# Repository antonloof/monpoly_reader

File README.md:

# monpoly_reader
Projekt ligger i det runda arkivet. RFID var krångligare än väntat
"the juice is not worth the squeze"

Spela monopol fast långsamare

och utan ett o

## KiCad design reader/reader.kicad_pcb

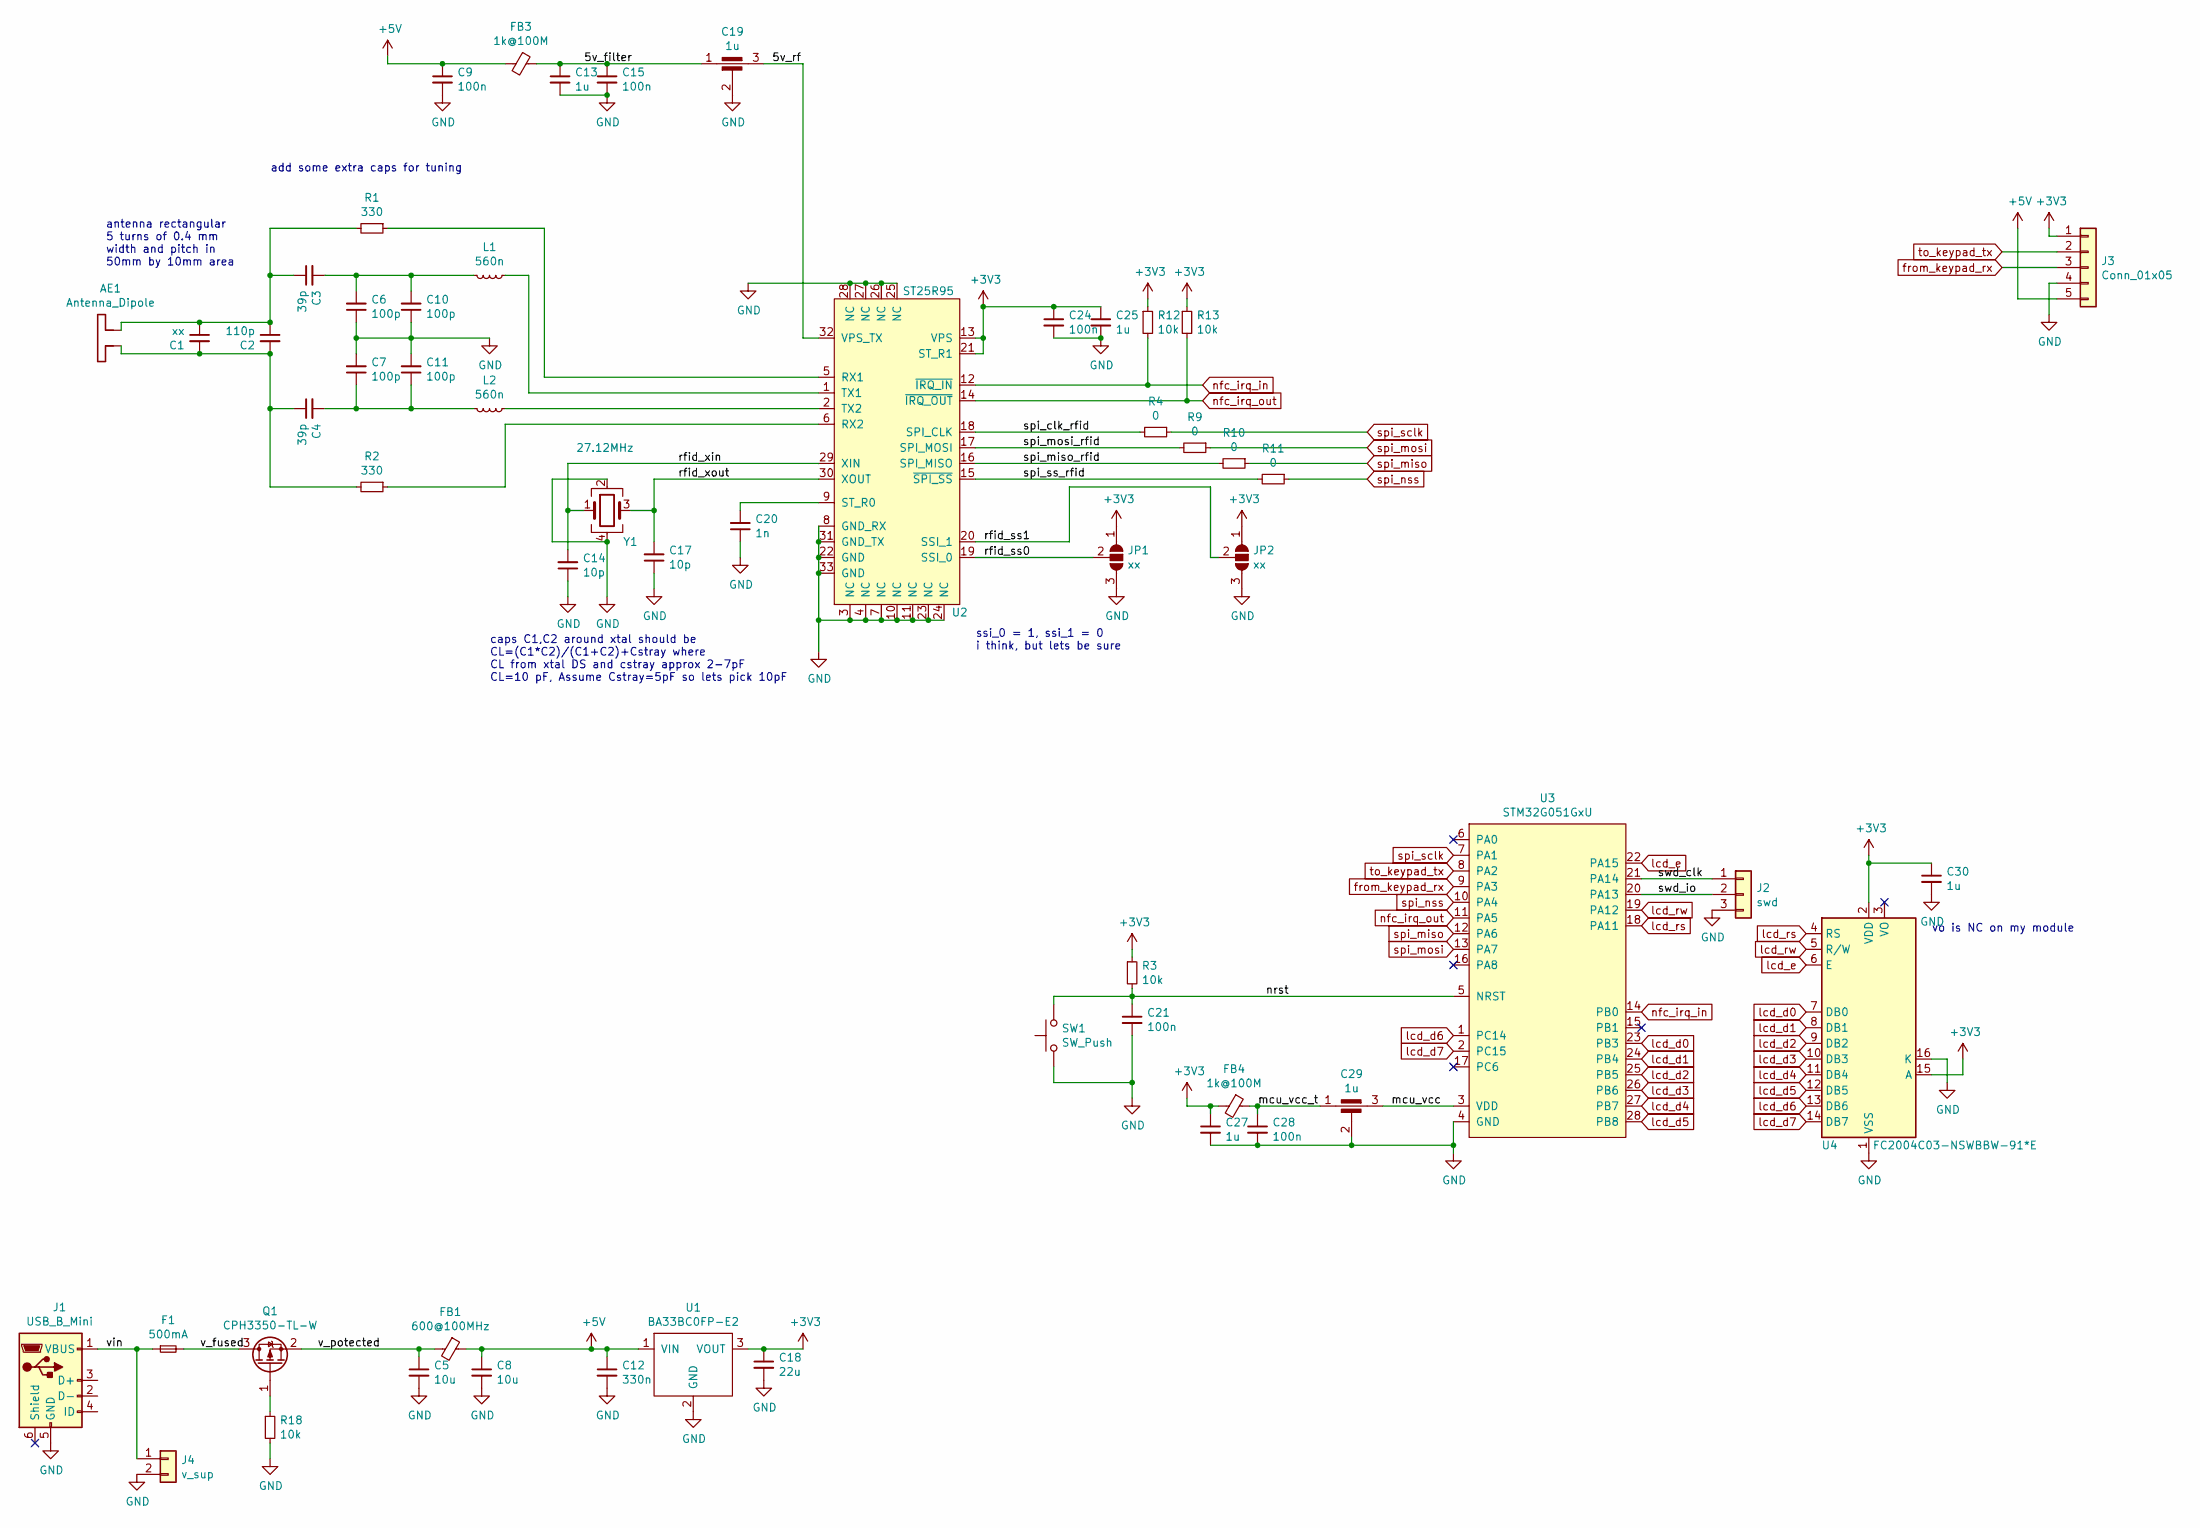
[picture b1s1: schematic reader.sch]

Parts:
AE1: Antenna_Dipole; antenna_1m_07mm_3turn
C1: xx; C_0603_1608Metric_Pad1.05x0.95mm_HandSolder
C2: 110p; C_0603_1608Metric_Pad1.05x0.95mm_HandSolder
C3, C4: 39p; C_0603_1608Metric_Pad1.05x0.95mm_HandSolder
C5, C8: 10u; C_0603_1608Metric_Pad1.05x0.95mm_HandSolder; farnell 3013453
C6, C7, C10, C11: 100p; C_0603_1608Metric_Pad1.05x0.95mm_HandSolder
C9, C15, C21, C24, C28: 100n; C_0603_1608Metric_Pad1.05x0.95mm_HandSolder
C12: 330n; C_0603_1608Metric_Pad1.05x0.95mm_HandSolder
C13, C27, C30: 1u; C_0603_1608Metric_Pad1.05x0.95mm_HandSolder; farnell 3013382
C14, C17: 10p; C_0603_1608Metric_Pad1.05x0.95mm_HandSolder
C18: 22u; C_0603_1608Metric_Pad1.05x0.95mm_HandSolder
C19, C29: 1u; NFM18PS105R0J3D
C20: 1n; C_0603_1608Metric_Pad1.05x0.95mm_HandSolder
C25: 1u; C_0603_1608Metric_Pad1.05x0.95mm_HandSolder
F1: 500mA; Fuse_1210_3225Metric
FB1: 600@100MHz; L_0603_1608Metric_Pad1.05x0.95mm_HandSolder
FB3, FB4: 1k@100M; L_0603_1608Metric_Pad1.05x0.95mm_HandSolder
J1: USB_B_Mini; USB_MICRO_10118193-0001LF
J2: swd; PinHeader_1x03_P2.54mm_Vertical
J3: Conn_01x05; PinHeader_1x05_P2.54mm_Vertical
J4: v_sup; JST_NV_B02P-NV_1x02_P5.00mm_Vertical
JP1, JP2: xx; SolderJumper-3_P1.3mm_Open_RoundedPad1.0x1.5mm
L1, L2: 560n; L_0805_2012Metric; farnell 2858966
Q1: CPH3350-TL-W; SOT-23_Handsoldering
R1, R2: 330; R_0603_1608Metric_Pad1.05x0.95mm_HandSolder
R3, R12, R13, R18: 10k; R_0603_1608Metric_Pad1.05x0.95mm_HandSolder
R4, R9, R10, R11: 0; R_0603_1608Metric_Pad1.05x0.95mm_HandSolder
SW1: SW_Push; push_sw_purple
U1: BA33BC0FP-E2; TO-252-3_TabPin2
U2: ST25R95; QFN-32-1EP_5x5mm_P0.5mm_EP3.65x3.65mm
U3: STM32G051GxU; QFN-28_4x4mm_P0.5mm
U4: FC2004C03-NSWBBW-91*E; FC2004C03-NSWBBW-91
Y1: 27.12MHz; Crystal_SMD_2016-4Pin_2.0x1.6mm

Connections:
+3V3: C18.1, C24.1, C25.1, C27.1, C30.1, FB4.2, J3.1, JP1.1 (A), JP2.1 (A), R3.1, R12.1, R13.1, U1.3 (VOUT), U2.13 (VPS), U2.21 (ST_R1), U4.2 (VDD), U4.15 (A)
+5V: C8.1, C9.1, C12.1, FB1.1, FB3.2, J3.5, U1.1 (VIN)
/5v_filter: C13.1, C15.1, C19.1, FB3.1
/5v_rf: C19.3, U2.32 (VPS_TX)
/mcu_vcc: C29.3, U3.3 (VDD)
/mcu_vcc_t: C28.1, C29.1, FB4.1
/nrst: C21.1, R3.2, SW1.2, U3.5 (NRST)
/rfid_ss0: JP1.2 (C), U2.19 (SSI_0)
/rfid_ss1: JP2.2 (C), U2.20 (SSI_1)
/rfid_xin: C14.2, U2.29 (XIN), Y1.1
/rfid_xout: C17.2, U2.30 (XOUT), Y1.3
/spi_clk_rfid: R4.2, U2.18 (SPI_CLK)
/spi_miso_rfid: R10.2, U2.16 (SPI_MISO)
/spi_mosi_rfid: R9.2, U2.17 (SPI_MOSI)
/spi_ss_rfid: R11.2, U2.15 (~SPI_SS)
/swd_clk: J2.1, U3.21 (PA14)
/swd_io: J2.2, U3.20 (PA13)
/v_fused: F1.2, Q1.3 (D)
/v_potected: C5.1, FB1.2, Q1.2 (S)
/vin: F1.1, J1.1 (VBUS), J4.1
GND: C5.2, C6.1, C7.2, C8.2, C9.2, C10.1, C11.2, C12.2, C13.2, C14.1, C15.2, C17.1, C18.2, C19.2, C20.1, C21.2, C24.2, C25.2, C27.2, C28.2, C29.2, C30.2, J1.5 (GND), J2.3, J3.4, J4.2, JP1.3 (B), JP2.3 (B), R18.2, SW1.1, U1.2 (GND), U2.3 (NC), U2.4 (NC), U2.7 (NC), U2.8 (GND_RX), U2.10 (NC), U2.11 (NC), U2.22 (GND), U2.23 (NC), U2.24 (NC), U2.25 (NC), U2.26 (NC), U2.27 (NC), U2.28 (NC), U2.31 (GND_TX), U2.33 (GND), U3.4 (GND), U4.1 (VSS), U4.16 (K), Y1.2, Y1.4
unnamed: AE1.1, C1.2, C2.2, C4.1, R2.2
unnamed: AE1.2, C1.1, C2.1, C3.1, R1.2
unnamed: C3.2, C6.2, C10.2, L1.2
unnamed: C4.2, C7.1, C11.1, L2.2
unnamed: C20.2, U2.9 (ST_R0)
unnamed: L1.1, U2.1 (TX1)
unnamed: L2.1, U2.2 (TX2)
unnamed: Q1.1 (G), R18.1
unnamed: R1.1, U2.5 (RX1)
unnamed: R2.1, U2.6 (RX2)
from_keypad_rx: J3.3, U3.9 (PA3)
lcd_d0: U3.23 (PB3), U4.7 (DB0)
lcd_d1: U3.24 (PB4), U4.8 (DB1)
lcd_d2: U3.25 (PB5), U4.9 (DB2)
lcd_d3: U3.26 (PB6), U4.10 (DB3)
lcd_d4: U3.27 (PB7), U4.11 (DB4)
lcd_d5: U3.28 (PB8), U4.12 (DB5)
lcd_d6: U3.1 (PC14), U4.13 (DB6)
lcd_d7: U3.2 (PC15), U4.14 (DB7)
lcd_e: U3.22 (PA15), U4.6 (E)
lcd_rs: U3.18 (PA11), U4.4 (RS)
lcd_rw: U3.19 (PA12), U4.5 (R/W)
nfc_irq_in: R12.2, U2.12 (~IRQ_IN), U3.14 (PB0)
nfc_irq_out: R13.2, U2.14 (~IRQ_OUT), U3.11 (PA5)
spi_miso: R10.1, U3.12 (PA6)
spi_mosi: R9.1, U3.13 (PA7)
spi_nss: R11.1, U3.10 (PA4)
spi_sclk: R4.1, U3.7 (PA1)
to_keypad_tx: J3.2, U3.8 (PA2)

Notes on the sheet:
add some extra caps for tuning
antenna rectangular 5 turns of 0.4 mm width and pitch in 50mm by 10mm area
ssi_0 = 1, ssi_1 = 0 i think, but lets be sure
caps C1,C2 around xtal should be CL=(C1*C2)/(C1+C2)+Cstray where CL from xtal DS and cstray approx 2-7pF CL=10 pF, Assume Cstray=5pF so lets pick 10pF
vo is NC on my module

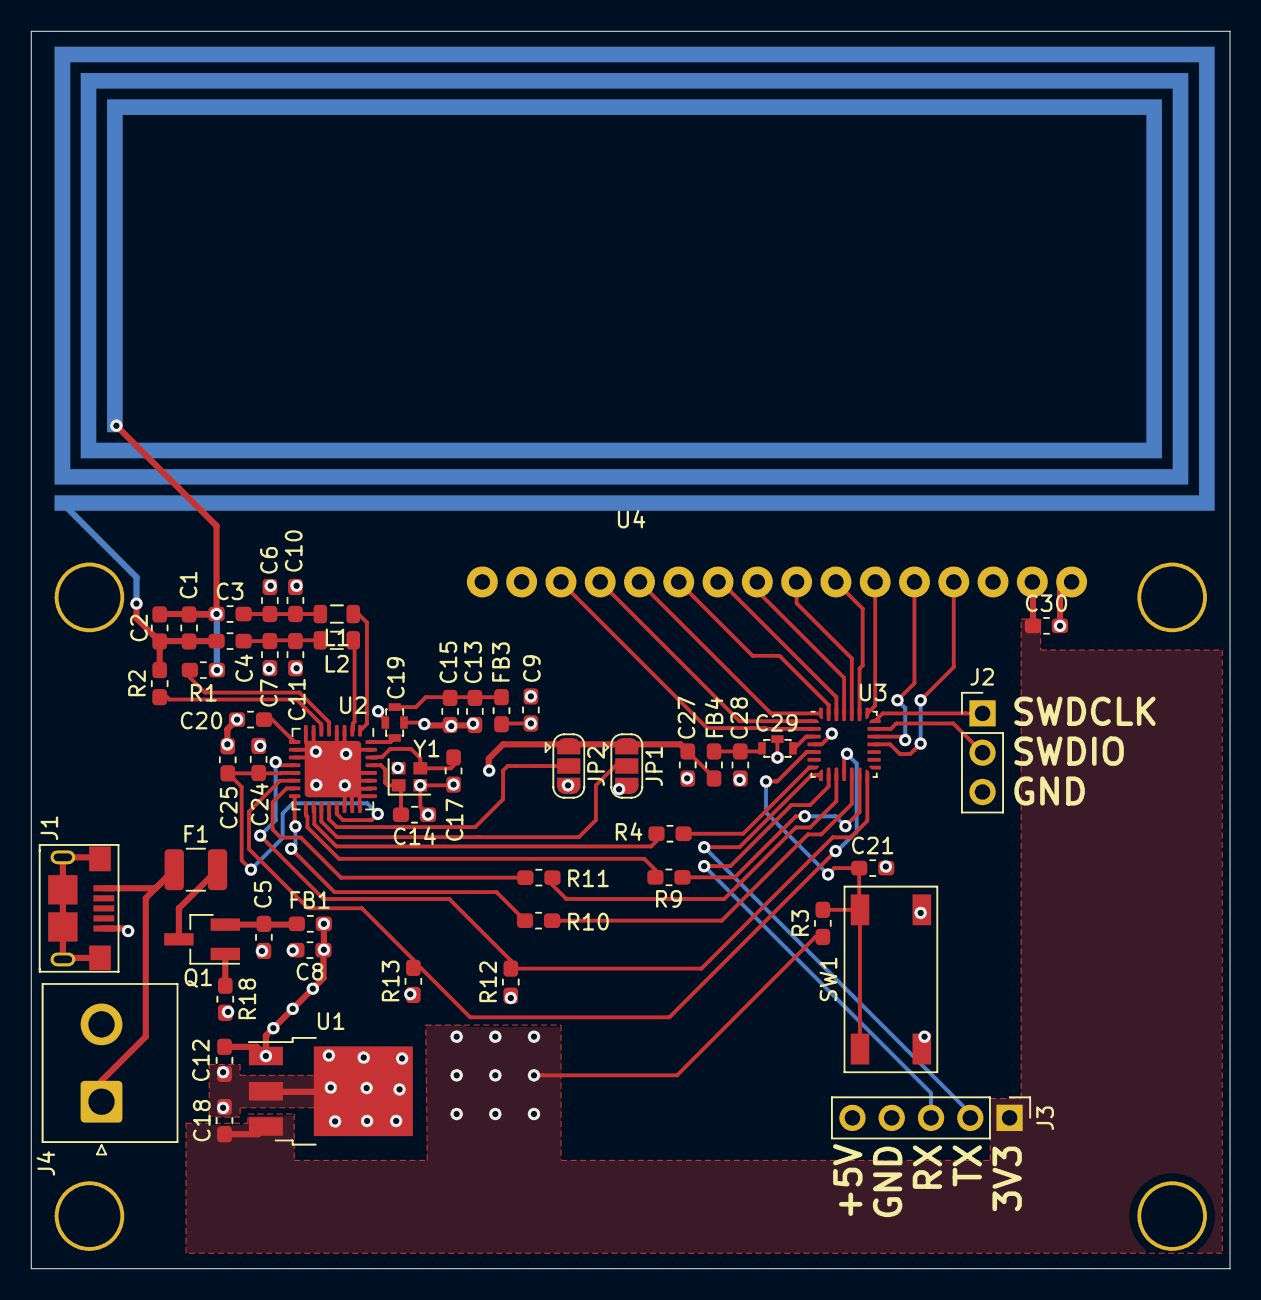
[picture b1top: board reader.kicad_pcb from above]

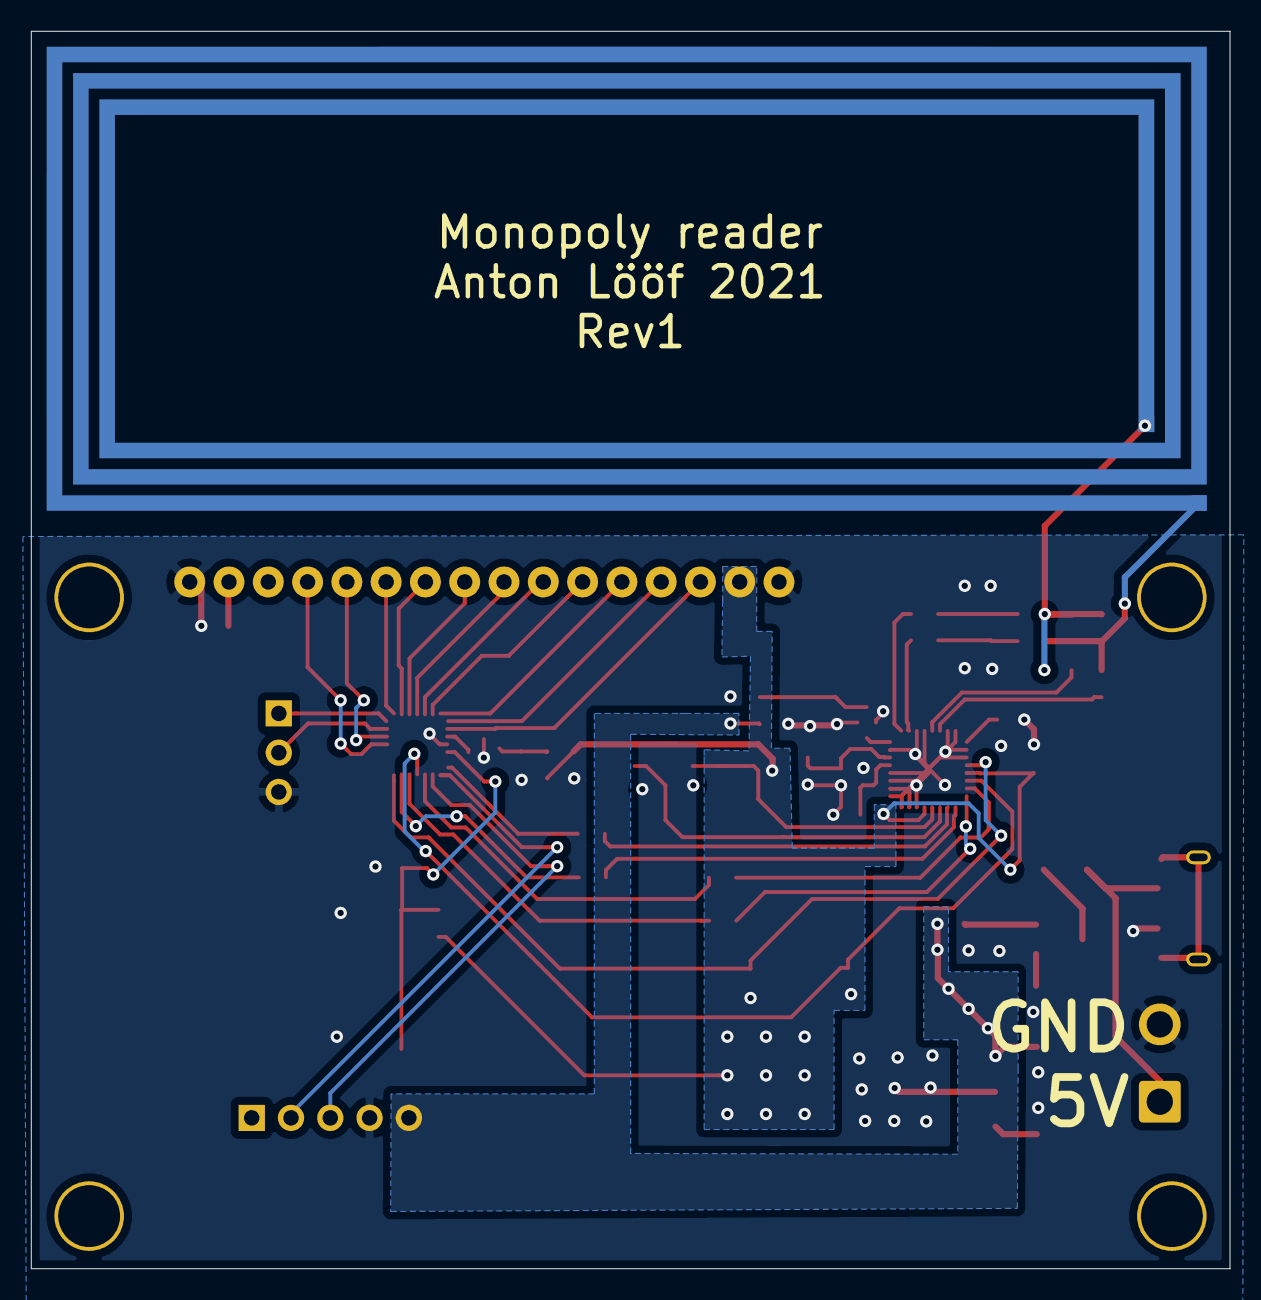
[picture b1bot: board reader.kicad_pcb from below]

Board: 2 copper layers, 77.5 x 80.0 mm, 56 parts (2 on the bottom side), 50 nets.

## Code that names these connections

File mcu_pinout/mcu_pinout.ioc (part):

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Mcu.Name=STM32G051G(6-8)Ux
Mcu.Package=UFQFPN28
Mcu.UserName=STM32G051G6Ux
PA1.Mode=Full_Duplex_Master
PA1.Signal=SPI1_SCK
PA11\ [PA9].GPIOParameters=GPIO_Label
PA11\ [PA9].GPIO_Label=lcd_rs
PA11\ [PA9].Signal=GPIO_Output
PA12\ [PA10].GPIOParameters=GPIO_Label
PA12\ [PA10].GPIO_Label=lcd_rw
PA12\ [PA10].Signal=GPIO_Output
PA13.Mode=Serial_Wire
PA13.Signal=SYS_SWDIO
PA14-BOOT0.Mode=Serial_Wire
PA14-BOOT0.Signal=SYS_SWCLK
PA15.GPIOParameters=GPIO_Label
PA15.GPIO_Label=lcd_e
PA15.Signal=GPIO_Output
PA2.Mode=Asynchronous
PA2.Signal=USART2_TX
PA3.Mode=Asynchronous
PA3.Signal=USART2_RX
PA4.Mode=NSS_Signal_Hard_Output
PA4.Signal=SPI1_NSS
PA5.GPIOParameters=GPIO_Label
PA5.GPIO_Label=nfc_int_out
PA5.Signal=GPXTI5
PA6.Mode=Full_Duplex_Master
PA6.Signal=SPI1_MISO
PA7.Mode=Full_Duplex_Master
PA7.Signal=SPI1_MOSI
PB0.GPIOParameters=GPIO_Label
PB0.GPIO_Label=nfc_int_in
PB0.Signal=GPIO_Output
PB3.GPIOParameters=GPIO_Label
PB3.GPIO_Label=lcd_d0
PB3.Signal=GPIO_Input
PB4.GPIOParameters=GPIO_Label
PB4.GPIO_Label=lcd_d1
PB4.Signal=GPIO_Input
PB5.GPIOParameters=GPIO_Label
PB5.GPIO_Label=lcd_d2
PB5.Signal=GPIO_Input
PB6.GPIOParameters=GPIO_Label
PB6.GPIO_Label=lcd_d3
PB6.Signal=GPIO_Input
PB7.GPIOParameters=GPIO_Label
PB7.GPIO_Label=lcd_d4
PB7.Signal=GPIO_Input
PB8.GPIOParameters=GPIO_Label
PB8.GPIO_Label=lcd_d5
PB8.Signal=GPIO_Input
PC14-OSC32_IN\ (PC14).GPIOParameters=GPIO_Label
PC14-OSC32_IN\ (PC14).GPIO_Label=lcd_d6
PC14-OSC32_IN\ (PC14).Signal=GPIO_Input
PC15-OSC32_OUT\ (PC15).GPIOParameters=GPIO_Label
PC15-OSC32_OUT\ (PC15).GPIO_Label=lcd_d7
PC15-OSC32_OUT\ (PC15).Signal=GPIO_Input
RCC.HSE_VALUE=8000000
RCC.SYSCLKFreq_VALUE=16000000
board=custom

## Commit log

2021-07-30 Add start of schematic
2021-07-30 förbättra readme
2021-10-07 Schema work
2021-10-09 Schema done
2021-10-10 Some placement and antenna
2021-10-12 Pcb read done
2021-10-13 Touchups of main board
    start design of keypad
    see https://www.thevfdcollective.com/blog/stm32-and-sk6812-rgbw-led
2021-10-13 rm unused
2021-10-13 Add keypad
2021-10-13 fix footprint of inductor
2021-10-13 Add proper mcu pinout and uart as output
2021-10-13 Dont forget to save
2021-10-14 Use solder bride instead of 0ohm
2022-01-06 Add sw
2022-01-08 Kill project
